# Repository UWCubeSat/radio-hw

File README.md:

# radio-hw

Work in progress OpenLST-based radio PCB with updated components.

## Pictures

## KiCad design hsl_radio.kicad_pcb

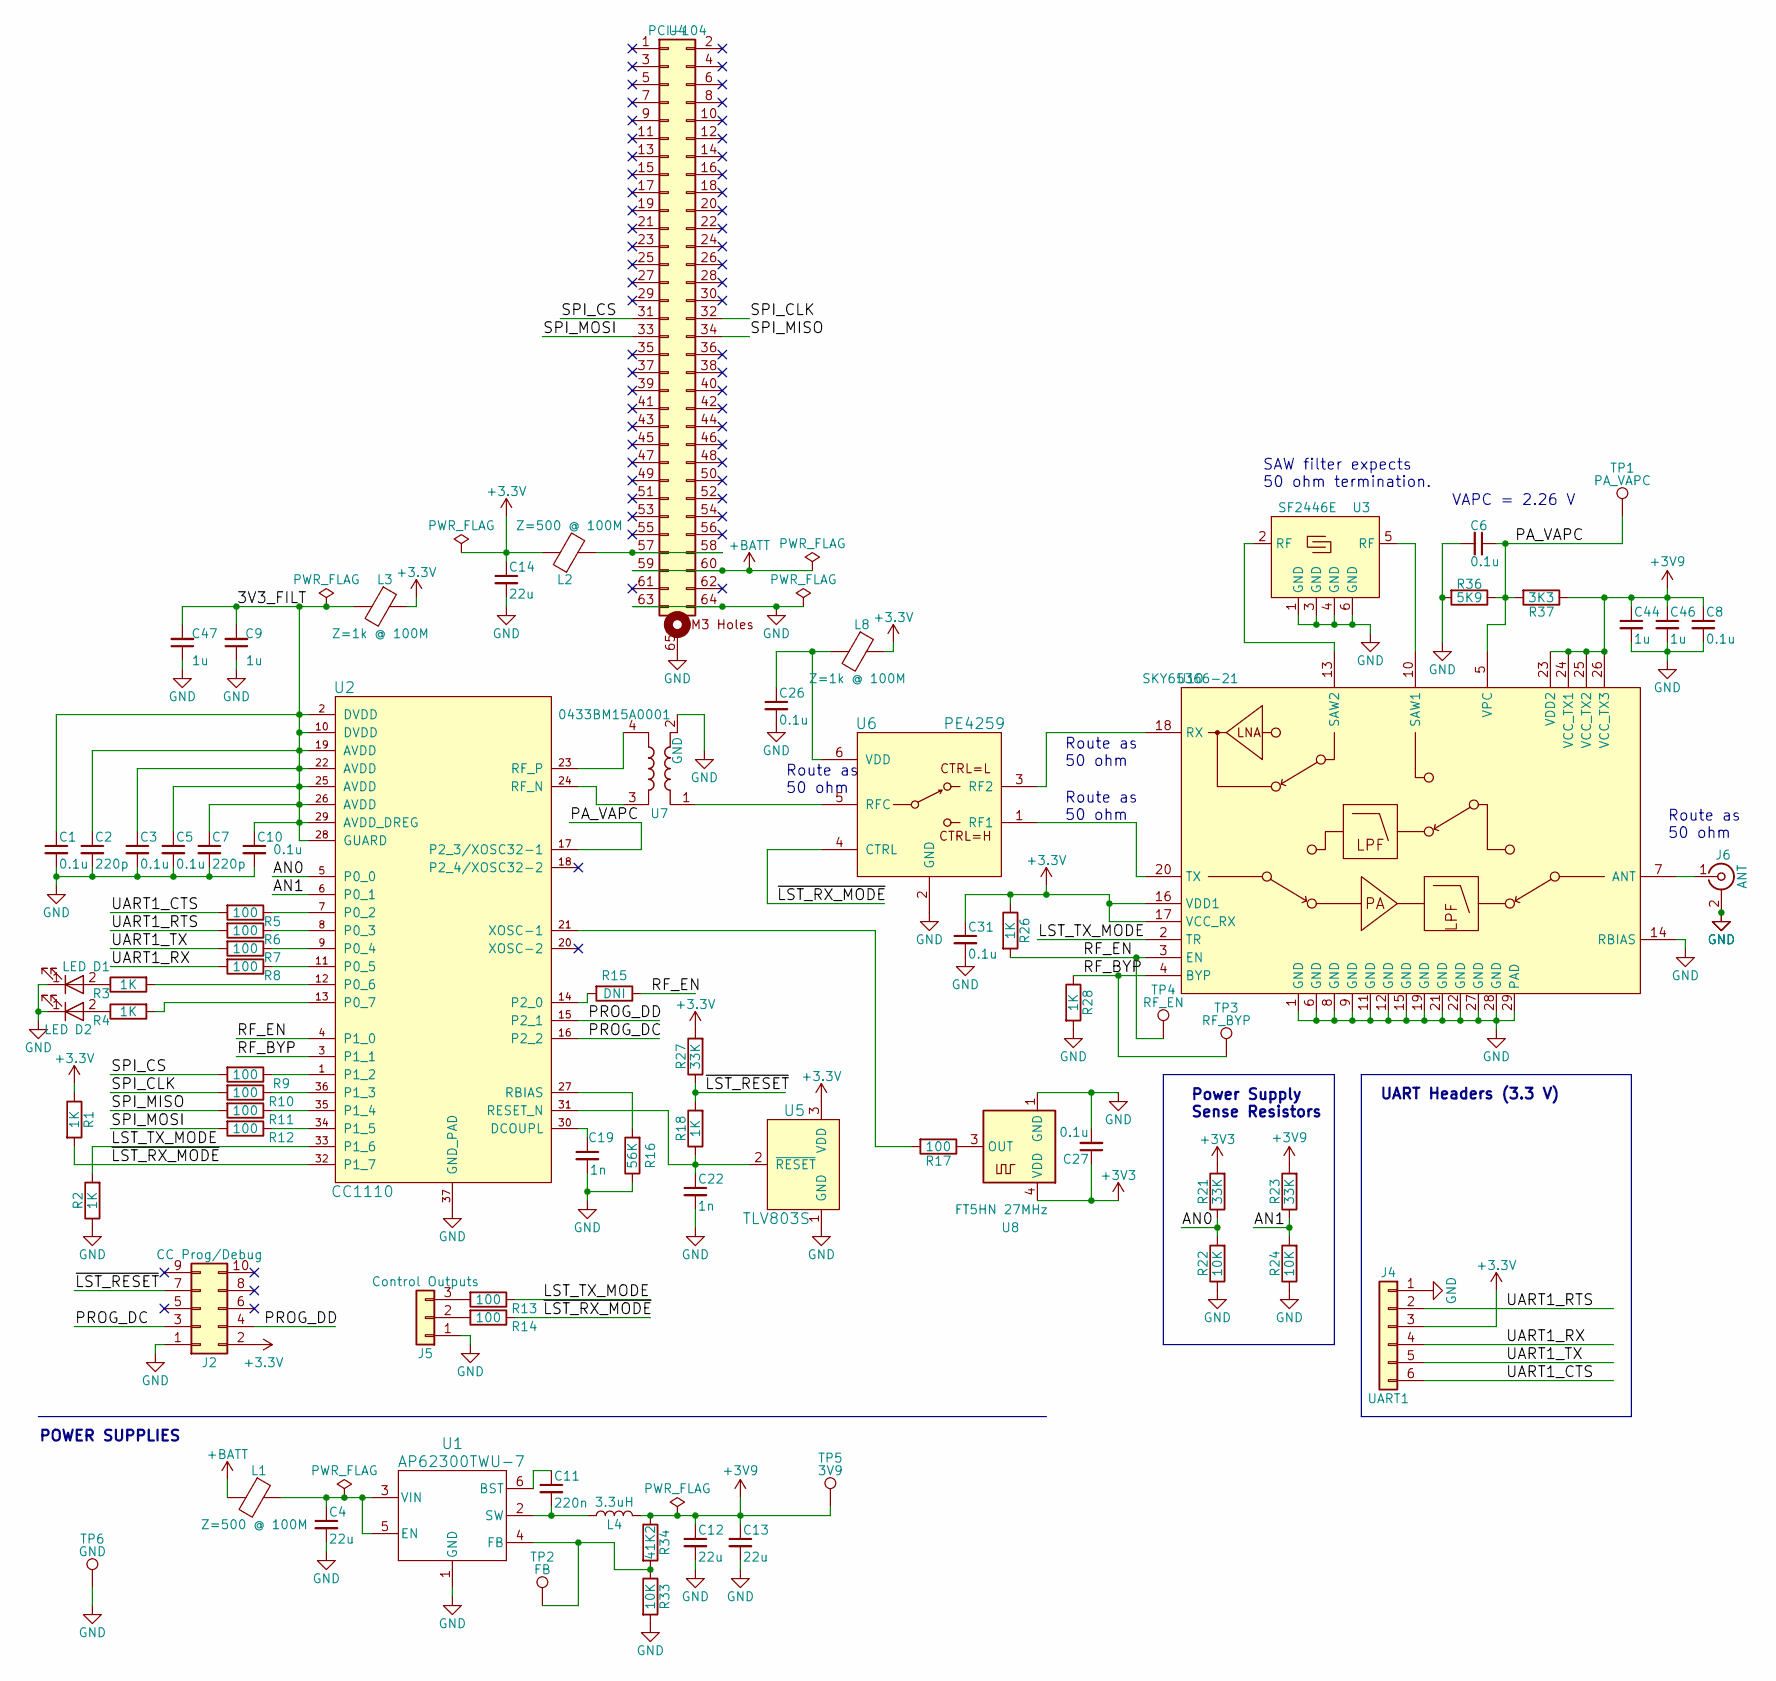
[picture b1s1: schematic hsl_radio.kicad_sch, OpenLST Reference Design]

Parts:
C1, C3, C5, C6, C8, C10, C26, C27, C31: 0.1u; C_0603_1608Metric; ManufPN 0603YC104K4T4A
C2, C7: 220p; C_0402_1005Metric; ManufPN C0402C221J2GACAUTO
C4, C12, C13, C14: 22u; C_0603_1608Metric
C9, C44, C46, C47: 1u; C_0603_1608Metric; ManufPN CL10B105MO8NNWC
C11: 220n; C_0603_1608Metric
C19, C22: 1n; C_0603_1608Metric; ManufPN GCM188R71E102KA37D
D1: LED; LED_0603_1608Metric; ManufPN 150060VS75000
D2: LED; LED_0603_1608Metric; ManufPN 150060SS75000
J2: CC Prog/Debug; PinHeader_2x05_P1.27mm_Vertical_SMD; ManufPN FTSH-105-01-L-DV-K-P
J4: UART1; PinHeader_1x06_P2.54mm_Vertical; ManufPN 61300611121
J5: Control Outputs; PinHeader_1x03_P2.54mm_Vertical
J6: ANT; SMA_Molex_73251-1153_EdgeMount_Horizontal; ManufPN 732511150
L1, L2: Z=500 @ 100M; L_1206_3216Metric; ManufPN MI1206L501R-10
L3, L8: Z=1k @ 100M; L_0603_1608Metric; ManufPN 74279266
L4: 3.3uH; L_TDK_VLS6045EX_VLS6045AF
R1, R2, R3, R4, R18, R26, R28: 1K; R_0603_1608Metric; ManufPN RC0603JR-071KL
R5, R6, R7, R8, R9, R10, R11, R12, R13, R14, R17: 100; R_0603_1608Metric; ManufPN AC0603FR-07100RL
R15: DNI; R_0603_1608Metric
R16: 56K; R_0603_1608Metric; ManufPN RMCF0603FT56K0
R21, R23, R27: 33K; R_0603_1608Metric; ManufPN AC0603FR-0733KL
R22, R24: 10K; R_0603_1608Metric; ManufPN RC0603JR-0710KL
R33: 10K; R_0603_1608Metric
R34: 41K2; R_0603_1608Metric
R36: 5K9; R_0603_1608Metric; ManufPN RMCF0603FT5K60
R37: 3K3; R_0603_1608Metric; ManufPN RMCF0603FT3K30
TP1: PA_VAPC; TestPoint_Pad_D2.0mm
TP2: FB; TestPoint_Pad_D2.0mm
TP3: RF_BYP; TestPoint_Pad_D2.0mm
TP4: RF_EN; TestPoint_Pad_D2.0mm
TP5: 3V9; TestPoint_Pad_D2.0mm
TP6: GND; TestPoint_Pad_D2.0mm
U1: AP62300TWU-7; TSOT26-WU_DIO
U2: CC1110; TI_CC_QFN36; ManufPN CC1110F32RHHR
U3: SF2446E
U4: PCI-104; PCI104
U5: TLV803S; SOT-23; ManufPN TLV803SDBZR
U6: PE4259; SOT-363_SC-70-6; ManufPN 4259-63
U7: 0433BM15A0001; Balun_Johanson_0896BM15A0001
U8: FT5HN 27MHz; Oscillator_SMD_Fox_FT5H_5.0x3.2mm
U10: SKY65366-21

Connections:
+3V9: C8.1, C12.1, C13.1, C44.1, C46.1, L4.2, R23.2, R34.1, R37.1, TP5.1, U10.23 (VDD2), U10.24 (VCC_TX1), U10.25 (VCC_TX2), U10.26 (VCC_TX3)
+BATT: L1.2, U4.59, U4.60
/3V3_FILT: C1.1, C2.1, C3.1, C5.1, C7.1, C9.2, C10.1, C47.2, L3.2, U2.2 (DVDD), U2.10 (DVDD), U2.19 (AVDD), U2.22 (AVDD), U2.25 (AVDD), U2.26 (AVDD), U2.28 (GUARD), U2.29 (AVDD_DREG)
/AN0: R21.1, R22.2, U2.5 (P0_0)
/AN1: R23.1, R24.2, U2.6 (P0_1)
/LST_TX_MODE: R2.2, R13.1, U2.33 (P1_6), U10.2 (TR)
/PA_VAPC: C6.1, R36.1, R37.2, TP1.1, U2.17 (P2_3/XOSC32-1), U10.5 (VPC)
/PROG_DC: J2.3, U2.16 (P2_2)
/PROG_DD: J2.4, U2.15 (P2_1)
/RF_BYP: R28.1, TP3.1, U2.3 (P1_1), U10.4 (BYP)
/RF_EN: R15.1, R26.2, TP4.1, U2.4 (P1_0), U10.3 (EN)
/SPI_CLK: R10.2, U4.32
/SPI_CS: R9.2, U4.31
/SPI_MISO: R11.2, U4.34
/SPI_MOSI: R12.2, U4.33
/UART1_CTS: J4.6, R5.2
/UART1_RTS: J4.2, R6.2
/UART1_RX: J4.4, R8.2
/UART1_TX: J4.5, R7.2
/~LST_RESET: J2.7, R18.2, R27.1
/~LST_RX_MODE: R1.2, R14.1, U2.32 (P1_7), U6.4 (CTRL)
GND: C1.2, C2.2, C3.2, C4.2, C5.2, C6.2, C7.2, C8.2, C9.1, C10.2, C12.2, C13.2, C14.2, C19.2, C22.2, C26.2, C27.2, C31.2, C44.2, C46.2, C47.1, D1.1 (K), D2.1 (K), J2.1, J4.1, J5.1, J6.2 (Ext), R2.1, R16.1, R22.1, R24.1, R28.2, R33.2, R36.2, TP6.1, U1.1 (GND), U2.37 (GND_PAD), U3.1 (GND), U3.3 (GND), U3.4 (GND), U3.6 (GND), U4.63, U4.64, U4.65 (Holes), U5.1 (GND), U6.2 (GND), U7.2 (GND), U7.5 (GND), U7.6 (GND), U8.1 (GND), U8.2 (GND), U10.1 (GND), U10.6 (GND), U10.8 (GND), U10.9 (GND), U10.11 (GND), U10.12 (GND), U10.14 (RBIAS), U10.15 (GND), U10.19 (GND), U10.21 (GND), U10.22 (GND), U10.27 (GND), U10.28 (GND), U10.29 (PAD)
unnamed: D1.2 (A), R3.1
unnamed: D2.2 (A), R4.1
unnamed: J5.2, R14.2
unnamed: J5.3, R13.2
unnamed: J6.1 (In), U10.7 (ANT)
unnamed: C11.1, U1.6 (BST)
unnamed: C4.1, L1.1, U1.3 (VIN), U1.5 (EN)
unnamed: R33.1, R34.2, TP2.1, U1.4 (FB)
unnamed: C11.2, L4.1, U1.2 (SW)
unnamed: C19.1, U2.30 (DCOUPL)
unnamed: R5.1, U2.7 (P0_2)
unnamed: R6.1, U2.8 (P0_3)
unnamed: R7.1, U2.9 (P0_4)
unnamed: R8.1, U2.11 (P0_5)
unnamed: R3.2, U2.12 (P0_6)
unnamed: R4.2, U2.13 (P0_7)
unnamed: R9.1, U2.1 (P1_2)
unnamed: R10.1, U2.36 (P1_3)
unnamed: R11.1, U2.35 (P1_4)
unnamed: R12.1, U2.34 (P1_5)
unnamed: R15.2, U2.14 (P2_0)
unnamed: R16.2, U2.27 (RBIAS)
unnamed: C22.1, R18.1, U2.31 (RESET_N), U5.2 (~RESET)
unnamed: U2.24 (RF_N), U7.3
unnamed: U2.23 (RF_P), U7.4
unnamed: R17.2, U2.21 (XOSC-1)
unnamed: L2.2, U4.57, U4.58
unnamed: U6.5 (RFC), U7.1
unnamed: C26.1, L8.2, U6.6 (VDD)
unnamed: R17.1, U8.3 (OUT)
unnamed: U6.3 (RF2), U10.18 (RX)
unnamed: U3.5 (RF), U10.10 (SAW1)
unnamed: U3.2 (RF), U10.13 (SAW2)
unnamed: U6.1 (RF1), U10.20 (TX)

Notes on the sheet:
UART Headers (3.3 V)
Route as 50 ohm
Power Supply Sense Resistors
POWER SUPPLIES
VAPC = 2.26 V
SAW filter expects 50 ohm termination.

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
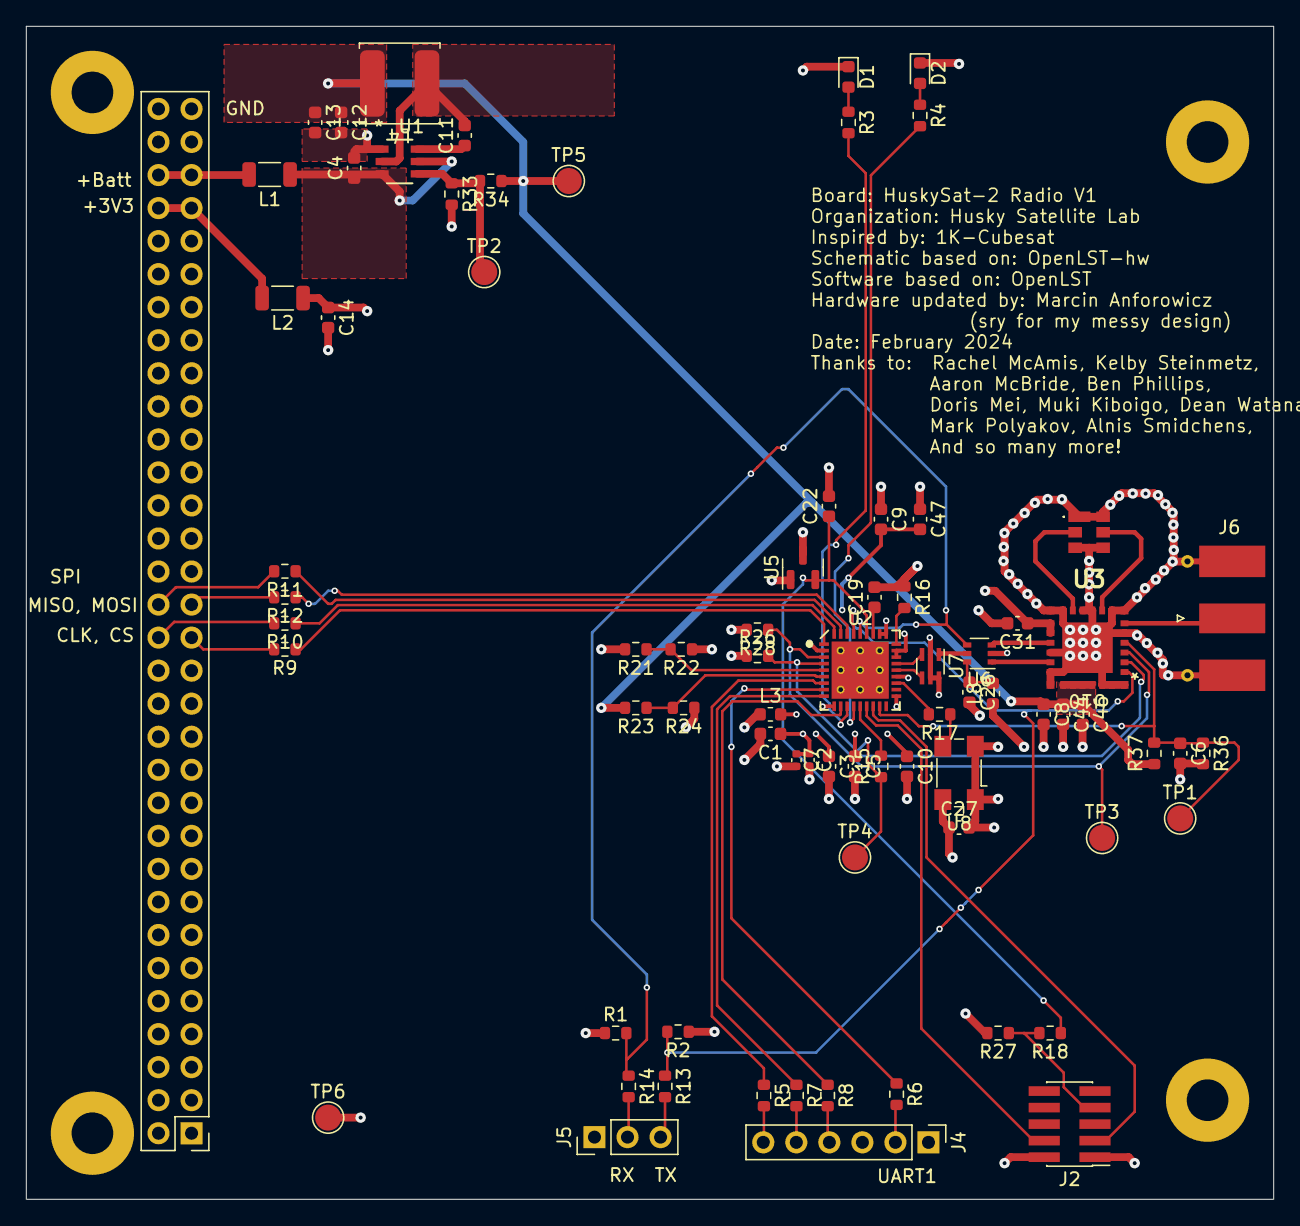
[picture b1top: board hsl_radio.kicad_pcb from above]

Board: 4 copper layers, 95.9 x 90.2 mm, 77 parts (0 on the bottom side), 57 nets.

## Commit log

2024-02-19 Removed outdated PDF
2024-02-19 Preparing for JLCPCB
2024-02-19 Generated manufacturing files
2024-02-23 Added test points
2024-02-23 Finalizing for JLCPCB
2024-02-27 Finalized things
2024-04-18 Add images to README

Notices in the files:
hsl_radio.kicad_sch:
This work is licensed under a Creative Commons Attribution-ShareAlike 4.0 International
Copyright 2018 Planet Labs Inc
